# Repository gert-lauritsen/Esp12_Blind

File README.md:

# ESP12 Blind Controller

## Oversigt

ESP12 Blind Controller er en WiFi-baseret rullegardinstyring udviklet til IKEA-rullegardiner med et 3D-printet gearsystem og en stepmotor. Enheden styres via MQTT og understøtter automatisk registrering i Home Assistant gennem MQTT Discovery.

Projektet er baseret på en ESP8266 (ESP-12) og kan drive både:

* 28BYJ-48 stepmotor via ULN2003 driver
* Kraftigere stepmotor via DRV8825 driver

Positionen gemmes i EEPROM, så gardinet bevarer sin position efter genstart.

---

## Funktioner

* WiFi-forbindelse med fast IP-adresse
* MQTT styring
* Home Assistant MQTT Discovery
* Gemmer top-, bund- og aktuel position i EEPROM
* Ikke-blokerende stepmotorstyring
* Understøtter procentvis positionering (0-100%)
* Understøtter OPEN, CLOSE og STOP kommandoer
* MQTT Last Will & Testament (Online/Offline status)
* Understøttelse af endestopkontakter
* Automatisk Home Assistant Device-oprettelse

---

## Hardware

### ESP8266

Projektet er udviklet til:

* ESP-12E
* ESP-12F
* NodeMCU
* Wemos D1 Mini

### Stepmotor

Anbefalet:

* 28BYJ-48 5V stepmotor

### Motor Driver

#### ULN2003

Standardkonfiguration:

| ESP8266 GPIO | ULN2003 |
| ------------ | ------- |
| GPIO5        | IN1     |
| GPIO0        | IN2     |
| GPIO4        | IN3     |
| GPIO2        | IN4     |

#### DRV8825

Alternativt kan projektet konfigureres til DRV8825 ved at deaktivere:

```cpp
#define ULN2003
```

og aktivere:

```cpp
#define DRV8825
```

---

## Endestopkontakter

Følgende indgange anvendes:

| Funktion      | GPIO |
| ------------- | ---- |
| Top Endestop  | D3   |
| Bund Endestop | D6   |

Begge anvender:

```cpp
INPUT_PULLUP
```

---

## Konfiguration

### secrets.h

Opret filen:

```cpp
#pragma once

#define WIFI_SSID   "MyWifi"
#define WIFI_PASS   "MyPassword"

#define MQTT_SERVER "192.168.1.10"
#define MQTT_USER   "mqttuser"
#define MQTT_PASS   "mqttpassword"

#define LOCAL_IP    192,168,1,50
#define GATEWAY_IP  192,168,1,1
#define SUBNET_MASK 255,255,255,0
```

---

## Valg af Gardin

Hvert gardin skal have et unikt navn.

Eksempel:

```cpp
const char* room = "bed_room_right";
```

Andre eksempler:

```cpp
const char* room = "living_room";
const char* room = "office";
const char* room = "kitchen";
```

Dette navn anvendes til:

* MQTT topics
* Home Assistant Device ID
* Home Assistant Entity Name

---

## MQTT Topics

Hvis:

```cpp
room = "bed_room_right"
```

oprettes følgende topics.

### Kommandoer

#### Åbn

Topic:

```text
home/blind/bed_room_right/set
```

Payload:

```text
OPEN
```

#### Luk

```text
CLOSE
```

#### Stop

```text
STOP
```

#### Gå til position

```text
50
```

Flytter gardinet til 50%.

---

### Direkte positionering

Topic:

```text
home/blind/bed_room_right/set_position
```

Payload:

```text
35000
```

Flytter direkte til step-position.

---

### Gem bundposition

Topic:

```text
home/blind/bed_room_right/save_bottom
```

Payload kan være tom.

Aktuel position gemmes som bundposition.

---

### Gem topposition

Topic:

```text
home/blind/bed_room_right/save_top
```

Payload kan være tom.

Aktuel position gemmes som topposition.

---

## Status Topics

### Position i procent

```text
home/blind/bed_room_right/state
```

Eksempel:

```text
75
```

### Aktuel step-position

```text
home/blind/bed_room_right/CurrentPosition
```

Eksempel:

```text
52341
```

### Tilgængelighed

```text
home/blind/bed_room_right/availability
```

Mulige værdier:

```text
online
offline
```

---

## Home Assistant

Projektet anvender MQTT Discovery.

Discovery Topic:

```text
homeassistant/cover/esp8266_blind_<room>/config
```

Ved opstart registreres gardinet automatisk som:

* Cover Entity
* Device
* Availability Sensor

Ingen manuel YAML-konfiguration er nødvendig.

---

## EEPROM

Følgende data gemmes permanent:

| Adresse | Data             |
| ------- | ---------------- |
| 0       | Bottom Position  |
| 4       | Top Position     |
| 8       | Current Position |

Data gemmes automatisk når:

* Top position ændres
* Bund position ændres
* Gardinet når sin destination

---

## Første Opstart

Ved første opstart initialiseres:

```cpp
bottomPosition = 0;
topPosition = 70000;
currentPosition = 0;
```

Disse værdier bør efterfølgende kalibreres.

---

## Kalibrering

1. Kør gardinet til helt lukket position.
2. Send MQTT kommando til:

```text
home/blind/<room>/save_bottom
```

3. Kør gardinet til helt åben position.
4. Send MQTT kommando til:

```text
home/blind/<room>/save_top
```

5. Positionerne gemmes i EEPROM.

---

## Netværk

Projektet anvender statisk IP-adresse.

Konfiguration:

```cpp
WiFi.config(local_IP, gateway, subnet);
```

Hvis DHCP ønskes kan denne linje fjernes.

---

## Seriel Debug

Baudrate:

```text
115200
```

Ved opstart vises blandt andet:

```text
Connecting to WiFi
MQTT host: 192.168.1.10
Setup Completed
AA:BB:CC:DD:EE:FF
```

---

## Projektstruktur

```text
Esp12_Blind/
│
├── README.md
├── Schematic.png
│
├── Esp8266_blindController_HA/
│   ├── Esp8266_blindController_HA.ino
│   └── secrets.h
│
└── ES3P2_test/
    └── Esp32_blindController_HA/
```

---

## Kendte Begrænsninger

* Automatisk kalibrering er ikke implementeret.
* Endestopkontakter anvendes endnu ikke aktivt under normal drift.
* Positionering er baseret på step-tælling og ikke absolut feedback.
* Ved mekanisk slip kan positionen afvige.

---

## Fremtidige Forbedringer

* Automatisk kalibrering via endestop
* Web-interface
* OTA firmwareopdatering
* Hastighedsramper (Acceleration/Deceleration)
* Batteridrift
* Position backup til MQTT/Home Assistant

## Noter
Simple rullegardin styring baseret på Ikea rulle gardin og et 3D printet gear. Driver en lille stepper vha ULN2003.
I den nye hardware har jeg lagt ind at man også kan bruge en almindelig stepper driver til lidt mere highpower stepper

- Video [On Smarthome](https://www.facebook.com/Askob.dk/photos/a.409725012772869/409724829439554/?type=3&theater)
- [608ZZ kugleleje](https://arduinotech.dk/shop/kuglelejer/)
- [28BYJ-48](https://arduinotech.dk/shop/step-gear-motor-28byj-48-5v-4-phase-5-wire-dc-5v/) stepper motor

- [Schematic](https://github.com/gert-lauritsen/Esp12_Blind/blob/master/ESP12DualStepperPCB/RulleGardin.pdf)

---

## Referencer

* ESP8266
* Home Assistant MQTT Discovery
* PubSubClient
* ArduinoJson
* 28BYJ-48 Stepper Motor
* ULN2003 Driver
* DRV8825 Driver

## Licens

Projektet stilles til rådighed som open source. Tilpas og anvend frit på eget ansvar.

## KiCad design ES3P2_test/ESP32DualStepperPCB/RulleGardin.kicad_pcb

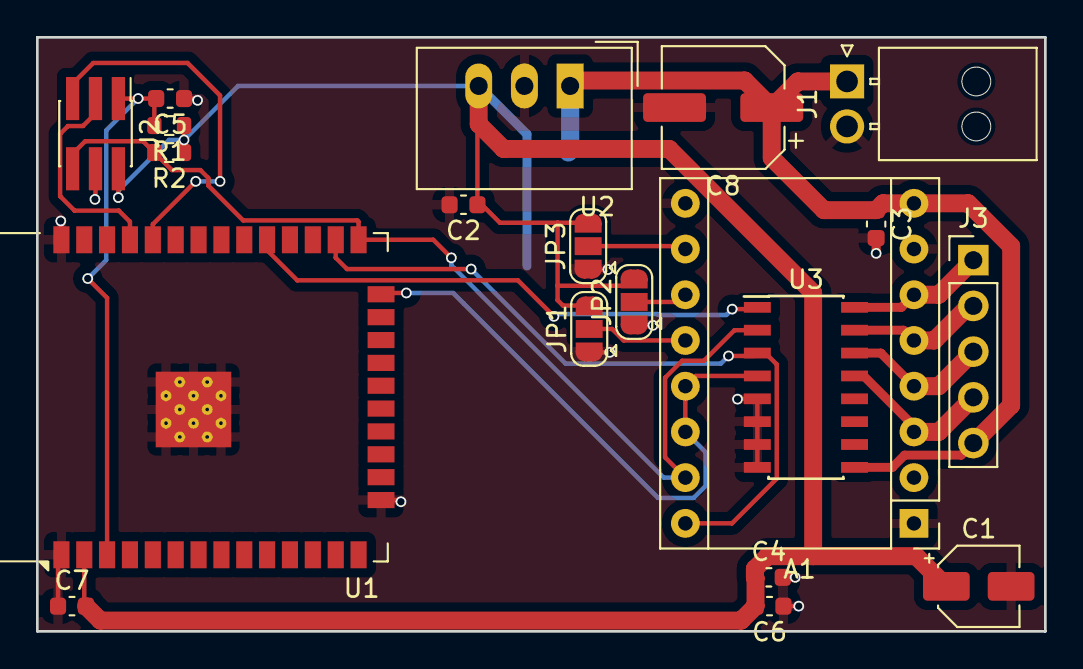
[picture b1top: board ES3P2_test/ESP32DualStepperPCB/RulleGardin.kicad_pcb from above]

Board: 2 copper layers, 56.0 x 33.0 mm, 21 parts (1 on the bottom side), 17 nets.

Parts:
A1: Pololu_Breakout_DRV8825; Pololu_Breakout-16_15.2x20.3mm
C1: 10u; CP_Elec_4x5.4
C2, C3, C4: 1uF; C_0603_1608Metric
C5, C6, C7: 0.1uf; C_0603_1608Metric
C8: 10u; CP_Elec_6.3x7.7
J1: Power; Molex_NanoFit_1x02x2.50mm_Angled
J2: Prog; PinHeader_2x03_P1.27mm_Vertical_SMD
J3: Conn_01x05; Pin_Header_Straight_1x05_Pitch2.54mm
JP1: jumper; SolderJumper-3_P1.3mm_Open_RoundedPad1.0x1.5mm
JP2, JP3: Jumper; SolderJumper-3_P1.3mm_Open_RoundedPad1.0x1.5mm
R1, R2: 10K; R_0603_1608Metric
U1: ESP32-WROOM-32
U2: TSR_1-2433; Converter_DCDC_TRACO_TSR-1_THT
U3: ULN2003A; SOIC-16_3.9x9.9mm_Pitch1.27mm
U4: AZ1117-3.3; SOT-223-3_TabPin2

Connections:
+3.3V: C1.1, C2.1, C4.1, C6.2, C7.2, J2.2, JP1.3 (B), JP2.3 (B), JP3.3 (B), R1.1, R2.1, U1.2 (VDD), U2.3 (Vout), U4.2 (VO)
+5V: A1.8 (VMOT), C3.1, C8.1, J1.1, J3.5, U2.1 (Vin), U3.9 (COM), U4.3 (VI)
/Coil1: A1.3 (A2), J3.4, U3.13 (O4)
/Coil2: A1.4 (A1), J3.3, U3.14 (O3)
/Coil3: A1.5 (B1), J3.2, U3.15 (O2)
/Coil4: A1.6 (B2), J3.1, U3.16 (O1)
/D2: A1.13 (~RST), A1.14 (~SLP), U1.24 (IO2), U3.4 (I4)
/D4: A1.16 (DIR), U1.26 (IO4), U3.3 (I3)
/D5: U1.29 (IO5), U3.1 (I1)
D0: A1.15 (STEP), J2.6, R2.2, U1.25 (IO0), U3.2 (I2)
EN: C5.2, J2.1, R1.2, U1.3 (EN)
GND: A1.1 (GND), A1.7 (GND), A1.9 (~EN), C1.2, C2.2, C3.2, C4.2, C5.1, C6.1, C7.1, C8.2, J1.2, J2.4, JP1.1 (A), JP2.1 (A), JP3.1 (A), U1.1 (GND), U1.15 (GND), U1.38 (GND), U1.39 (GND), U2.2 (GND), U3.5 (I5), U3.6 (I6), U3.7 (I7), U3.8 (GND), U4.1 (GND)
unnamed: A1.10 (M0), JP3.2 (C)
unnamed: A1.11 (M1), JP2.2 (C)
unnamed: A1.12 (M2), JP1.2 (C)
RX: J2.5, U1.34 (RXD0/IO3)
TX: J2.3, U1.35 (TXD0/IO1)

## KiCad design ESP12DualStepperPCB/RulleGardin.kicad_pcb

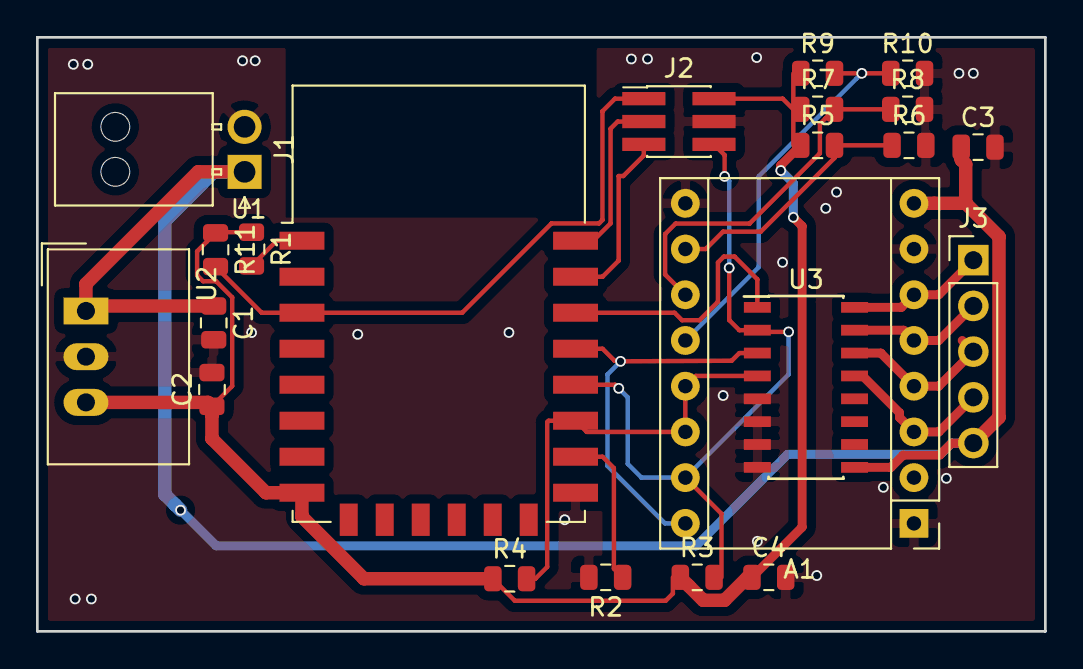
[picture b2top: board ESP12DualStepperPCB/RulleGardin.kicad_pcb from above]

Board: 2 copper layers, 56.0 x 33.0 mm, 22 parts (0 on the bottom side), 19 nets.

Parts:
A1: Pololu_Breakout_DRV8825; Pololu_Breakout-16_15.2x20.3mm
C1, C2: 22uF; C_0805_2012Metric
C3: 1uF; C_0805_2012Metric
C4: 1Uf; C_0805_2012Metric
J1: Power; Molex_NanoFit_1x02x2.50mm_Angled
J2: Conn_02x03_Odd_Even; Pin_Header_Straight_2x03_Pitch1.27mm_SMD
J3: Conn_01x05; Pin_Header_Straight_1x05_Pitch2.54mm
R1, R2, R11: 1k; R_0805_2012Metric
R3, R4: 10k; R_0805_2012Metric
R5, R6, R7, R8, R9, R10: NM; R_0805_2012Metric
U1: ESP-12E
U2: TSR_1-2433; Converter_DCDC_TRACO_TSR-1_THT
U3: ULN2003A; SOIC-16_3.9x9.9mm_Pitch1.27mm

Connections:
+3V3: C2.1, C4.1, J2.2, R1.1, R3.1, R4.1, R5.1, R7.1, R9.1, R11.1, U1.8, U2.3
+5V: A1.8, C1.1, C3.1, J1.1, J3.5, U2.1, U3.9
/Coil1: A1.3, J3.4, U3.13
/Coil2: A1.4, J3.3, U3.14
/Coil3: A1.5, J3.2, U3.15
/Coil4: A1.6, J3.1, U3.16
/D0: A1.15, J2.6, R3.2, U1.18, U3.2
/D2: A1.13, A1.14, R4.2, U1.17, U3.4
/D4: A1.16, U1.19, U3.3
/D5: U1.20, U3.1
/EN: J2.1, R11.2, U1.3
/RX: J2.5, U1.21
/TX: J2.3, U1.22
GNDD: A1.1, A1.7, A1.9, C1.2, C2.2, C3.2, C4.2, J1.2, J2.4, R2.2, R6.2, R8.2, R10.2, U1.15, U2.2, U3.5, U3.6, U3.7, U3.8
unnamed: A1.10, R5.2, R6.1
unnamed: A1.11, R7.2, R8.1
unnamed: A1.12, R9.2, R10.1
unnamed: R1.2, U1.1
unnamed: R2.1, U1.16

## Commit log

2020-11-19 init
2025-04-12 start af HA integration
2025-04-13 HA integration completed
2025-04-13 cleanup
2025-04-13 PCB update
2025-04-14 rettet de sidste fejl
2025-04-15 client name has to be uniq
2025-04-15 Added ESP32 Since esp8266 dont work with my router
2025-04-15 fund that its the dhcp that the problem, so now with static IP
2025-04-16 updatePCB
2026-02-24 med device understøttelse
